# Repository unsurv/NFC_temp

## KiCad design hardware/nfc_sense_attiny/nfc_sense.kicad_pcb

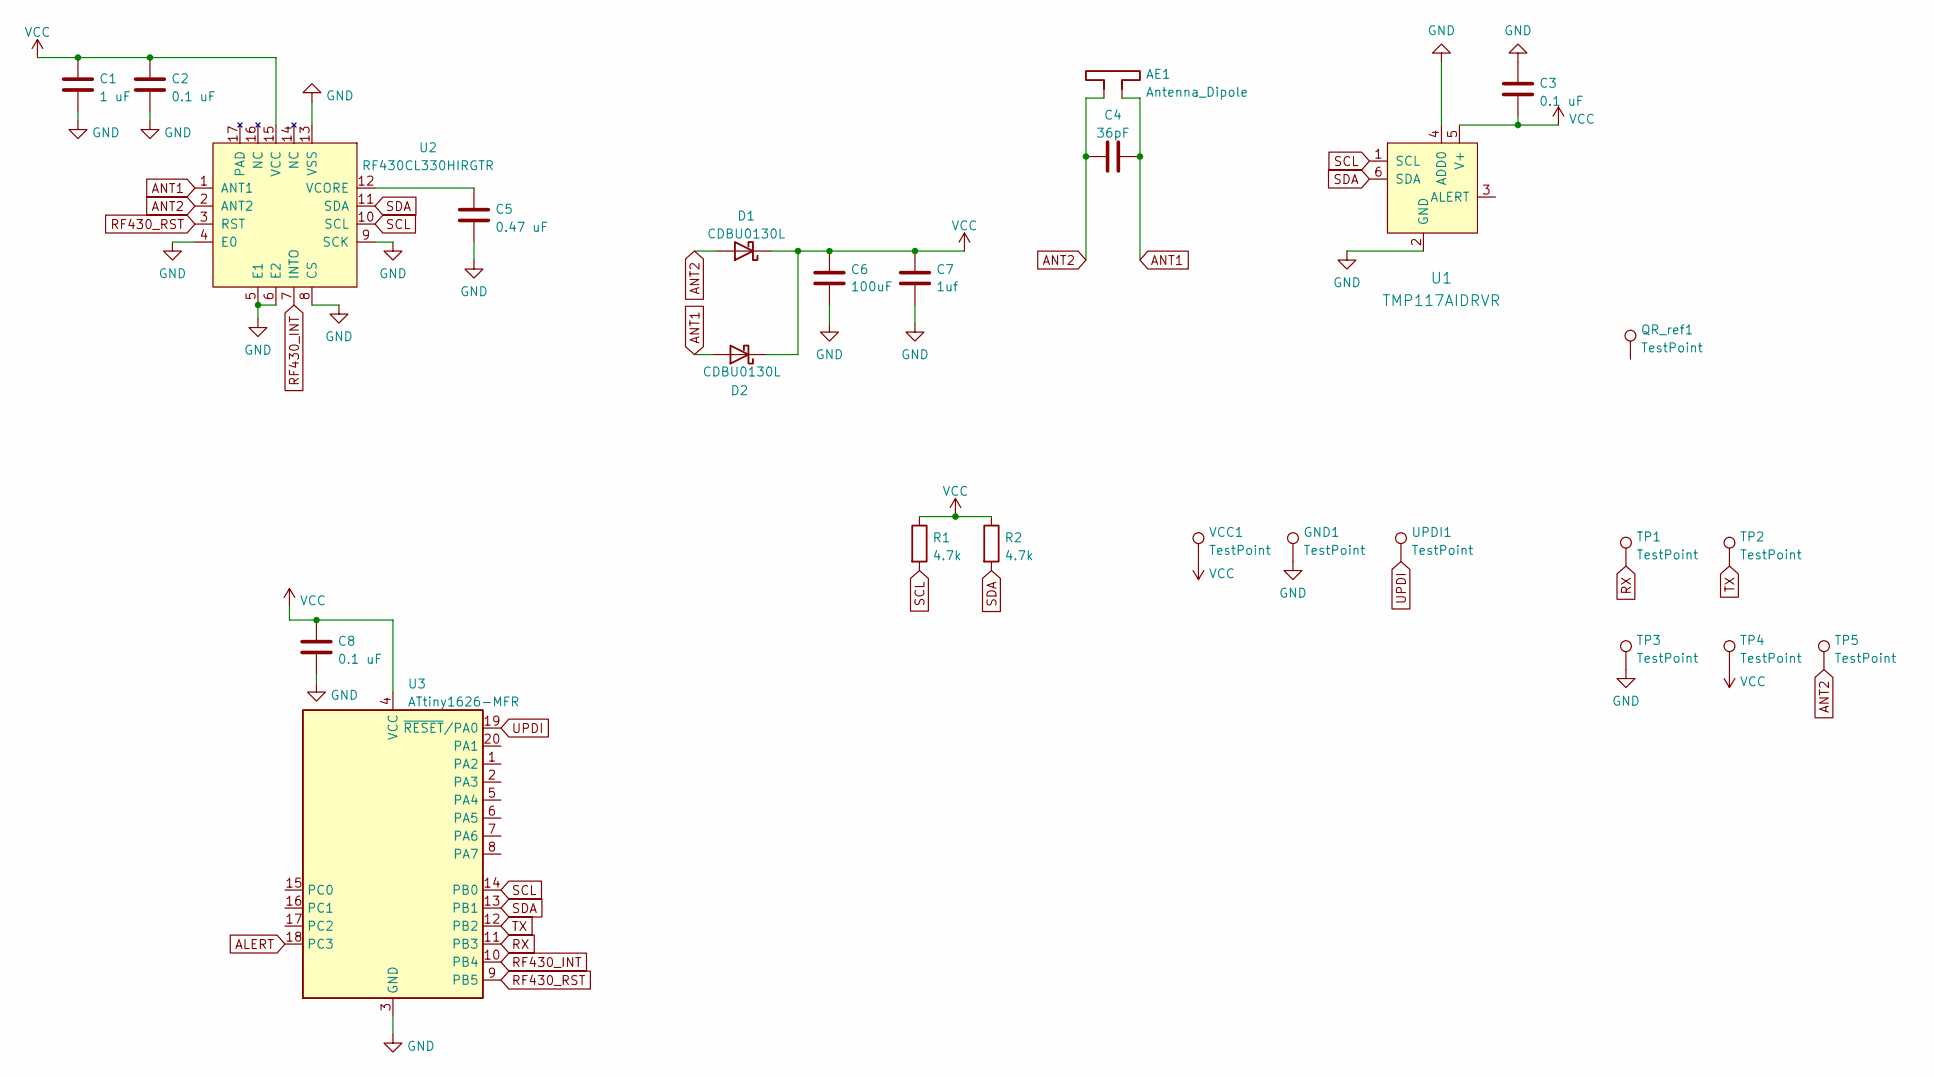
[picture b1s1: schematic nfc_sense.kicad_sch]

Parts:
AE1: Antenna_Dipole; 35_18_1_9nH
C1: 1 uF; C_0603_1608Metric
C2, C8: 0.1 uF; C_0603_1608Metric
C3: 0.1 uF; C_0402_1005Metric
C4: 36pF; C_0402_1005Metric
C5: 0.47 uF; C_0603_1608Metric
C6: 100uF; C_0603_1608Metric; MPN 298W107X0004M2T
C7: 1uf; C_0603_1608Metric
D1, D2: CDBU0130L; D_0603_1608Metric
GND1: TestPoint; TestPoint_Pad_D1.0mm
QR_ref1: TestPoint; QR_shop
R1, R2: 4.7k; R_0603_1608Metric
TP1, TP2, TP3, TP4, TP5: TestPoint; TestPoint_Pad_D1.0mm
U1: TMP117AIDRVR; TMP117 WSON-6-1EP_2x2mm_P0.65mm_no_pad_paste; MPN TMP117AIDRVR; Digi-Key_PN 296-24621-1-ND
U2: RF430CL330HIRGTR‎; RF430_3x3mm_regular
U3: ATtiny1626-MFR; VQFN-20-1EP_3x3mm_P0.4mm_EP1.7x1.7mm_edited
UPDI1: TestPoint; TestPoint_Pad_D1.0mm
VCC1: TestPoint; TestPoint_Pad_D1.0mm

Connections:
ALERT: U3.18 (PC3)
ANT1: AE1.1, C4.2, D2.2 (A), U2.1 (ANT1)
ANT2: AE1.2, C4.1, D1.2 (A), TP5.1, U2.2 (ANT2)
GND: C1.2, C2.2, C3.2, C5.2, C6.2, C7.2, C8.2, GND1.1, TP3.1, U1.2 (GND), U1.4 (ADD0), U2.4 (E0), U2.5 (E1), U2.6 (E2), U2.8 (CS), U2.9 (SCK), U2.13 (VSS), U3.3 (GND), U3.21 (GND)
unnamed: C5.1, U2.12 (VCORE)
RF430_INT: U2.7 (INTO), U3.10 (PB4)
RF430_RST: U2.3 (RST), U3.9 (PB5)
RX: TP1.1, U3.11 (PB3)
SCL: R1.2, U1.1 (SCL), U2.10 (SCL), U3.14 (PB0)
SDA: R2.2, U1.6 (SDA), U2.11 (SDA), U3.13 (PB1)
TX: TP2.1, U3.12 (PB2)
UPDI: U3.19 (~RESET/PA0), UPDI1.1
VCC: C1.1, C2.1, C3.1, C6.1, C7.1, C8.1, D1.1 (K), D2.1 (K), R1.1, R2.1, TP4.1, U1.5 (V+), U2.15 (VCC), U3.4 (VCC), VCC1.1

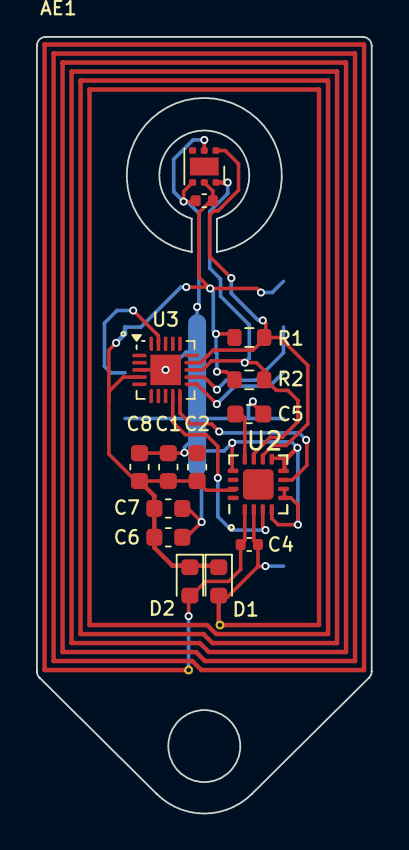
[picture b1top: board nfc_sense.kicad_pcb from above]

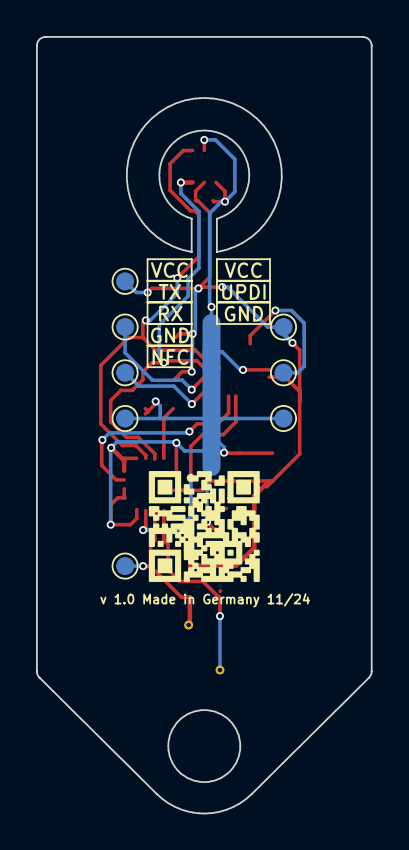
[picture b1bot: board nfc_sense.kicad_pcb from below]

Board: 4 copper layers, 18.6 x 43.1 mm, 25 parts (9 on the bottom side), 12 nets.
